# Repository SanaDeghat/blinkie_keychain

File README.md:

# blinkie_keychain
SO this is my blienkie for stasis X Sleepover 

Schematic:
https://lapse.hackclub.com/timelapse/7XoJm4L7D92-

Finihed the PCB too this is super small but this was the challange so i couldnt do harder stuff anyways she looks so cute (plus first tiem submittign to a hardware hackathon so kinda exited ) (and the lapse link:https://lapse.hackclub.com/timelapse/znWMSynJAcWA)

anyways thats it thx yaal

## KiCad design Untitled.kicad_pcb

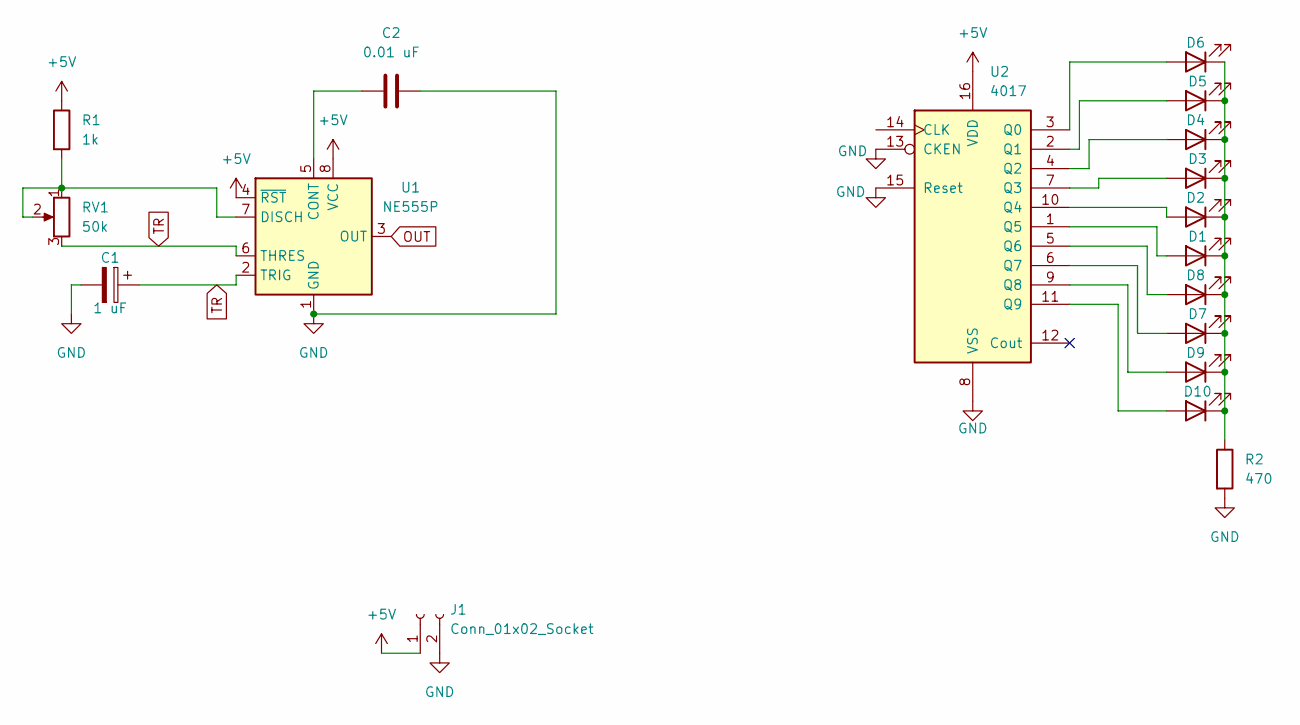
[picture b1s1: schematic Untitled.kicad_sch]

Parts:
C1: 1 uF; CP_Radial_D5.0mm_P2.00mm
C2: 0.01 uF; C_Disc_D7.5mm_W2.5mm_P5.00mm
D1, D2, D3, D4, D5, D6, D7, D8, D9, D10: LED; LED_D3.0mm
J1: Conn_01x02_Socket; PinHeader_1x02_P2.54mm_Vertical
R1: 1k; R_Axial_DIN0207_L6.3mm_D2.5mm_P7.62mm_Horizontal
R2: 470; R_Axial_DIN0207_L6.3mm_D2.5mm_P7.62mm_Horizontal
RV1: 50k; Potentiometer_Vishay_T93YA_Vertical
U1: NE555P; DIP-8_W7.62mm
U2: 4017; CD4017BE

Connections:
+5V: J1.1, R1.1, U1.4 (~RST), U1.8 (VCC), U2.16 (VDD)
GND: C1.2, C2.2, J1.2, R2.2, U1.1 (GND), U2.8 (VSS), U2.13 (CKEN), U2.15 (Reset)
unnamed: D1.2 (A), U2.1 (Q5)
unnamed: D1.1 (K), D2.1 (K), D3.1 (K), D4.1 (K), D5.1 (K), D6.1 (K), D7.1 (K), D8.1 (K), D9.1 (K), D10.1 (K), R2.1
unnamed: D2.2 (A), U2.10 (Q4)
unnamed: D3.2 (A), U2.7 (Q3)
unnamed: D4.2 (A), U2.4 (Q2)
unnamed: D5.2 (A), U2.2 (Q1)
unnamed: D6.2 (A), U2.3 (Q0)
unnamed: D7.2 (A), U2.6 (Q7)
unnamed: D8.2 (A), U2.5 (Q6)
unnamed: D9.2 (A), U2.9 (Q8)
unnamed: D10.2 (A), U2.11 (Q9)
unnamed: C2.1, U1.5 (CONT)
unnamed: R1.2, RV1.1, RV1.2, U1.7 (DISCH)
OUT: U1.3 (OUT)
TR: C1.1, RV1.3, U1.2 (TRIG), U1.6 (THRES)

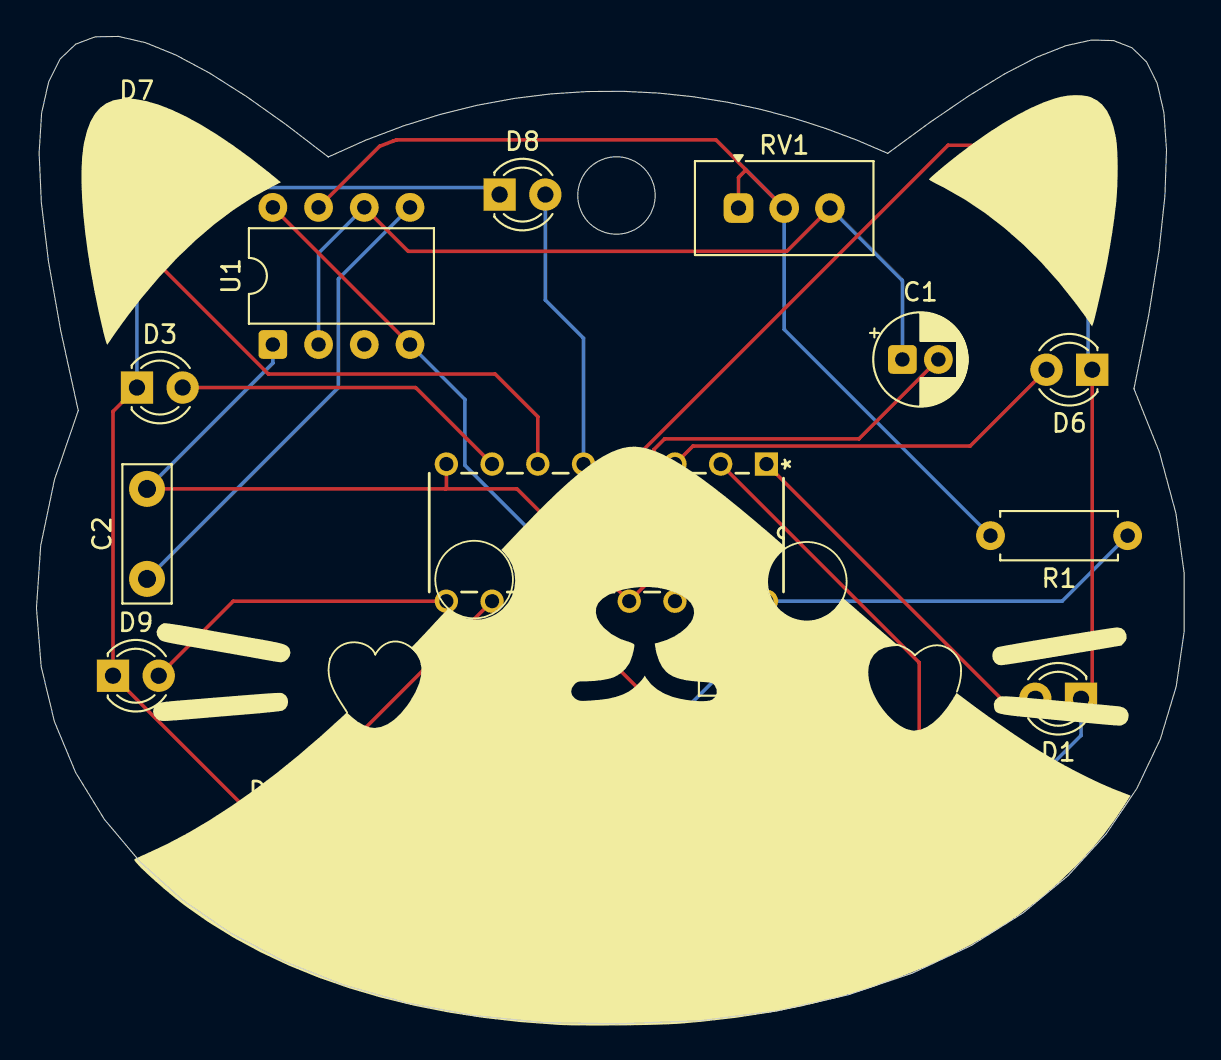
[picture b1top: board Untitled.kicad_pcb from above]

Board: 2 copper layers, 63.8 x 54.9 mm, 18 parts (0 on the bottom side), 16 nets.

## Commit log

2026-04-09 Schematic done
2026-04-09 update read me wit hschematic info
    Added project description and schematic images.
2026-04-09 pcb done
2026-04-09 Update README with PCB updates
    such diverse vocabilery i have
2026-04-09 forgot the lapse link
2026-04-09 generated grb files

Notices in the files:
parts and their libraries:
Copyright 2016 Accelerated Designs. All rights reserved.
